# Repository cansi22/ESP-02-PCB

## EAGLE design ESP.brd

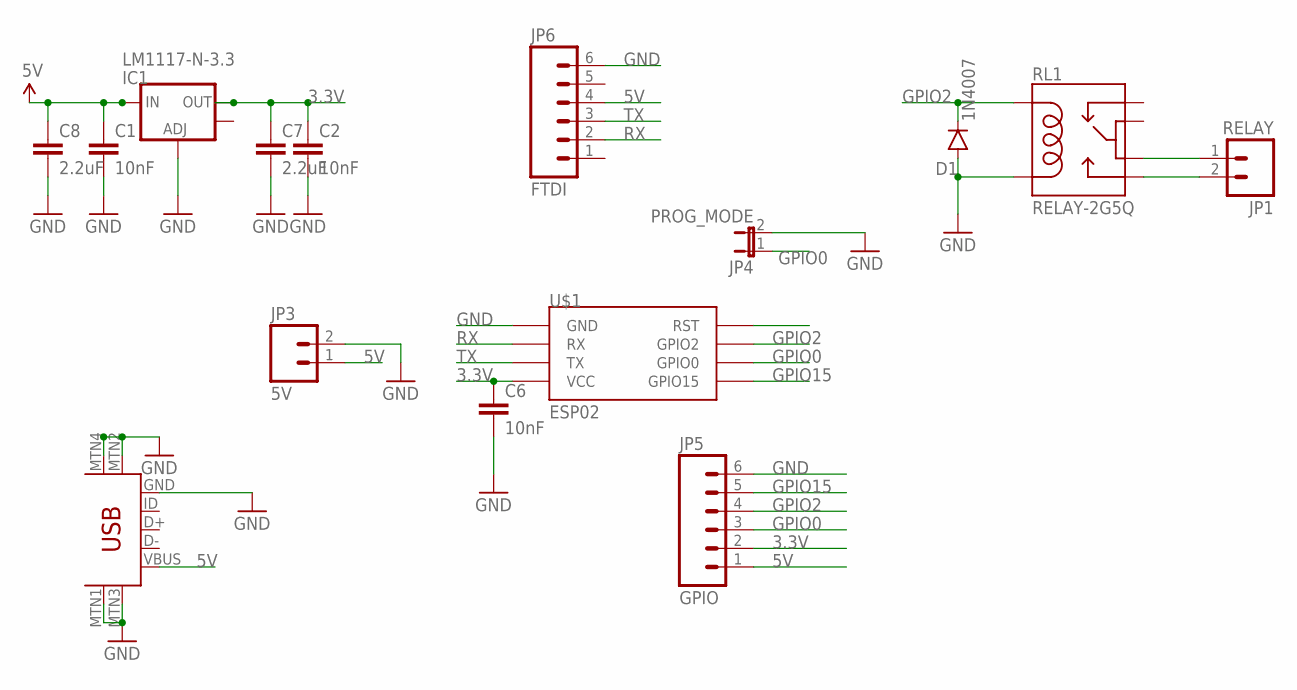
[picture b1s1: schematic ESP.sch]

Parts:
C1, C2, C6: 10nF; 0603-CAP
C7, C8: 2.2uF; 0805
D1: 1N4007; SMB-DIODE
IC1: LM1117-N-3.3; SOT223
JP1: RELAY; SCREWTERMINAL-5MM-2
JP3: 5V; SCREWTERMINAL-5MM-2
JP4: PROG_MODE; 1X02
JP5: GPIO; 1X06
JP6: FTDI; 1X06
RL1: RELAY-2G5Q; RELAY-G5V
U$1: ESP02
U$2: USB; USB-MINIB

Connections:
3.3V: C2.1, C6.1, C7.1, IC1.2 (OUT), JP5.2, U$1.VCC
5V: C1.1, C8.1, IC1.3 (IN), JP3.1, JP5.1, JP6.4, U$2.VBUS
GND: C1.2, C2.2, C6.2, C7.2, C8.2, D1.A, IC1.1 (ADJ), JP3.2, JP4.2, JP5.6, JP6.6, RL1.9, U$1.GND, U$2.GND, U$2.MTN1 (MTN2), U$2.MTN2 (MTN3), U$2.MTN3 (MTN1), U$2.MTN4
GPIO0: JP4.1, JP5.3, U$1.GPIO0
GPIO2: D1.C, JP5.4, RL1.2, U$1.GPIO2
GPIO15: JP5.5, U$1.GPIO15/POWERDOWN (GPIO15)
unnamed: JP1.2, RL1.10
unnamed: JP1.1, RL1.6
RX: JP6.2, U$1.RX
TX: JP6.3, U$1.TX

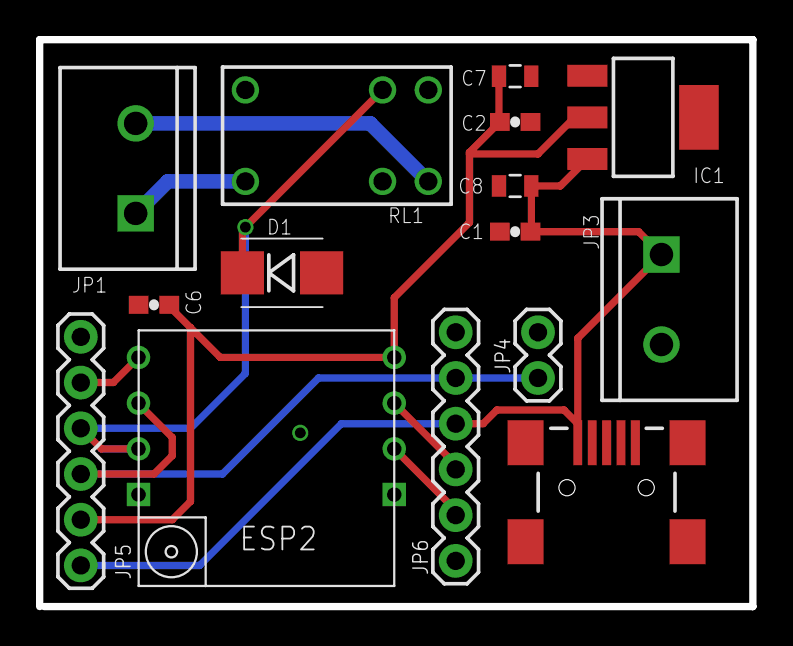
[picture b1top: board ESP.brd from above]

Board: 2 copper layers, 39.6 x 31.5 mm, 16 parts (1 on the bottom side), 10 nets.

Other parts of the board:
U$3: SL

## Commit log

2015-07-21 :neckbeard: Added .gitattributes
2015-07-21 ESP 02 PCB Relay
    PCB with GPIO, Relay and FTDI connector to program it
2015-07-21 Revert "ESP 02 PCB Relay"
    This reverts commit 73feaa8542858db9a8631ba49ea4a2a168d69517.
2015-07-21 Version 1.0

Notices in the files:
parts and their libraries:
SparkFun-Capacitors: Licensing: Creative Commons ShareAlike 4.0 International - https://creativecommons.org/licenses/by-sa/4.0
